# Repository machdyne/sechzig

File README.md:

# Sechzig Compute Module

Sechzig is a work-in-progress compute module specification.

Sechzig modules have a 60-pin 2.54mm card edge connector.

This repo contains detailed specifications as well as relevant KiCad symbols and footprints.

## Specifications

### Signals

This section describes the signals from the perspective of the module when paired with [Mozart](https://github.com/machdyne/mozart).

| Signal | Voltage | Dir | Description |
| ------ | ------- | --- | ----------- |
| PWR5V0 | 5.0V | I | System power (2A max) |
| PWR3V3 | 3.3V | I | System power (1A max) |
| PWRIO | 2.5V - 3.3V | O | I/O power (1A max) |
| SYS\_PG | 3.3V | I | System power good |
| SYS\_RST\_N | PWRIO | I | System reset (active low) |
| SYS\_CLK48 | PWRIO | I | System clock (48MHz) |
| USBD\_Dx | 3.3V | IO | USB device interface |
| USBHx\_Dx | 3.3V | IO | USB host interfaces |
| AUD\_DAT | PWRIO | O | Audio data |
| AUD\_BCK | PWRIO | O | Audio clock |
| AUD\_WS | PWRIO | O | Audio word select |
| ETH\_TXx | PWRIO | O | Ethernet RMII PHY transmit data |
| ETH\_RXx | PWRIO | I | Ethernet RMII PHY receive data |
| ETH\_TXEN | PWRIO | O | Ethernet RMII PHY transmit enable |
| ETH\_CRS\_DV | PWRIO | I | Ethernet RMII PHY carrier sense / receive data valid |
| ETH\_RST\_N | PWRIO | O | Ethernet RMII PHY reset (active low) |
| ETH\_CLK50 | PWRIO | I | Ethernet/video clock (50MHz) |
| DDMI\_xx\_x | 3.3V | O | [DDMI](https://github.com/machdyne/ddmi) interface |
| Xx | PWRIO | IO | Extra link (see notes below) |
| SD\_CD\_N | 3.3V | I | SD card detect (active low) |
| SD\_SS | 3.3V | IO | SD slave select / DAT3 |
| SD\_SCK | 3.3V | O | SD clock |
| SD\_MISO | 3.3V | IO | SD data output / DAT0 |
| SD\_MOSI | 3.3V | IO | SD data input / CMD |
| SD\_D1 | 3.3V| IO | SD DAT1 |
| SD\_D2 | 3.3V | IO | SD DAT2 |
| JTAG\_xxx | PWRIO | IO | JTAG interface |
| UART\_TX | PWRIO | O | UART transmit |
| UART\_RX | PWRIO | I | UART receive |
| DSx\_x | 2.5V | IO | Experimental high-speed link (see notes below) |

#### Signal Notes

  * While all Sechzig modules should be compatible with [Mozart](https://github.com/machdyne/mozart), it is possible to develop alternative host boards that use some signals for other purposes (see [Vivaldi](https://github.com/machdyne/vivaldi) and [Chopin](https://github.com/machdyne/chopin)).

##### Extra Link (Xx) Notes

The purpose of the Xx signals is determined by the host board. For example, on Mozart:

| Signal | Description |
| ------ | ----------- |
| XA | SPI MISO / I2C SCL |
| XB | SPI SCK / I2C SDA |
| XC | SPI MOSI |
| XD | SPI SS |

##### Experimental High-Speed Link (DSx) Notes

The DSx signal traces are routed as length-matched 100 ohm differential pairs. The following minimum required configuration should be supported by all modules, but some modules may have additional capabilities:

| Signal | Standard | Dir | Required | Description |
| ------ | -------- | --- | -------- | ----------- |
| DS0\_x | LVDS25 | IO | N | Transmit and/or Receive |
| DS1\_x | LVDS25 | O | Y | Transmit |
| DS2\_x | LVDS25 | I | Y | Receive |

### Power

Sechzig modules can operate with 2.5V or 3.3V I/O (note that some signals must be 2.5V and 3.3V on all modules). Modules that use 3.3V I/O can simply connect PWRIO to PWR3V3. Modules that use 2.5V I/O must provide 2.5V on PWRIO.

### Module Dimensions

| Dimension | Value |
| --------- | ----- |
| Width | 79mm |
| Height | 50mm max |
| Depth | 8mm max (4mm from center) |
| Card Edge Depth | 1.4mm - 1.6mm |

### Board Revisions

The version number can be found on the back of the module.

#### ML1

Product page for [Sechzig ML1](https://machdyne.com/product/sechzig-ml1-compute-module/).

| Revision | Stackup | Notes |
| -------- | ------- | ----- |
| ML1.1 | Aisler 4L | Initial production version; **Xx signals are not connected** |
| ML1.2 | Aisler 4L | Current production version; connects Xx signals; adds LED |

#### ML2

Product page for [Sechzig ML2](https://machdyne.com/product/sechzig-ml2-compute-module/).

| Revision | Stackup | Notes |
| -------- | ------- | ----- |
| ML2.0 | Aisler 6L | Initial production version |
| ML2.0B | JLC06161H-3313 | Current production version |

#### MX1

Product page for [Sechzig MX1](https://machdyne.com/product/sechzig-mx1-compute-module/).

| Revision | Stackup | Notes |
| -------- | ------- | ----- |
| MX1.1 | Aisler 4L | Initial production version |

#### MX2

Product page for [Sechzig MX2](https://machdyne.com/product/sechzig-mx2-compute-module/).

| Revision | Stackup | Notes |
| -------- | ------- | ----- |
| MX2.0 | JLC06161H-3313 | Initial production version |

## Funding

This project was partially funded through the NGI0 Entrust Fund, a fund established by NLnet with financial support from the European Commission's Next Generation Internet programme.

## License

This project is released under the [CERN-OHL-P](LICENSE.txt) license.

Note: You can use these designs for commercial purposes but we ask that instead of producing exact clones, that you either replace our trademarks and logos with your own or add your own next to ours.

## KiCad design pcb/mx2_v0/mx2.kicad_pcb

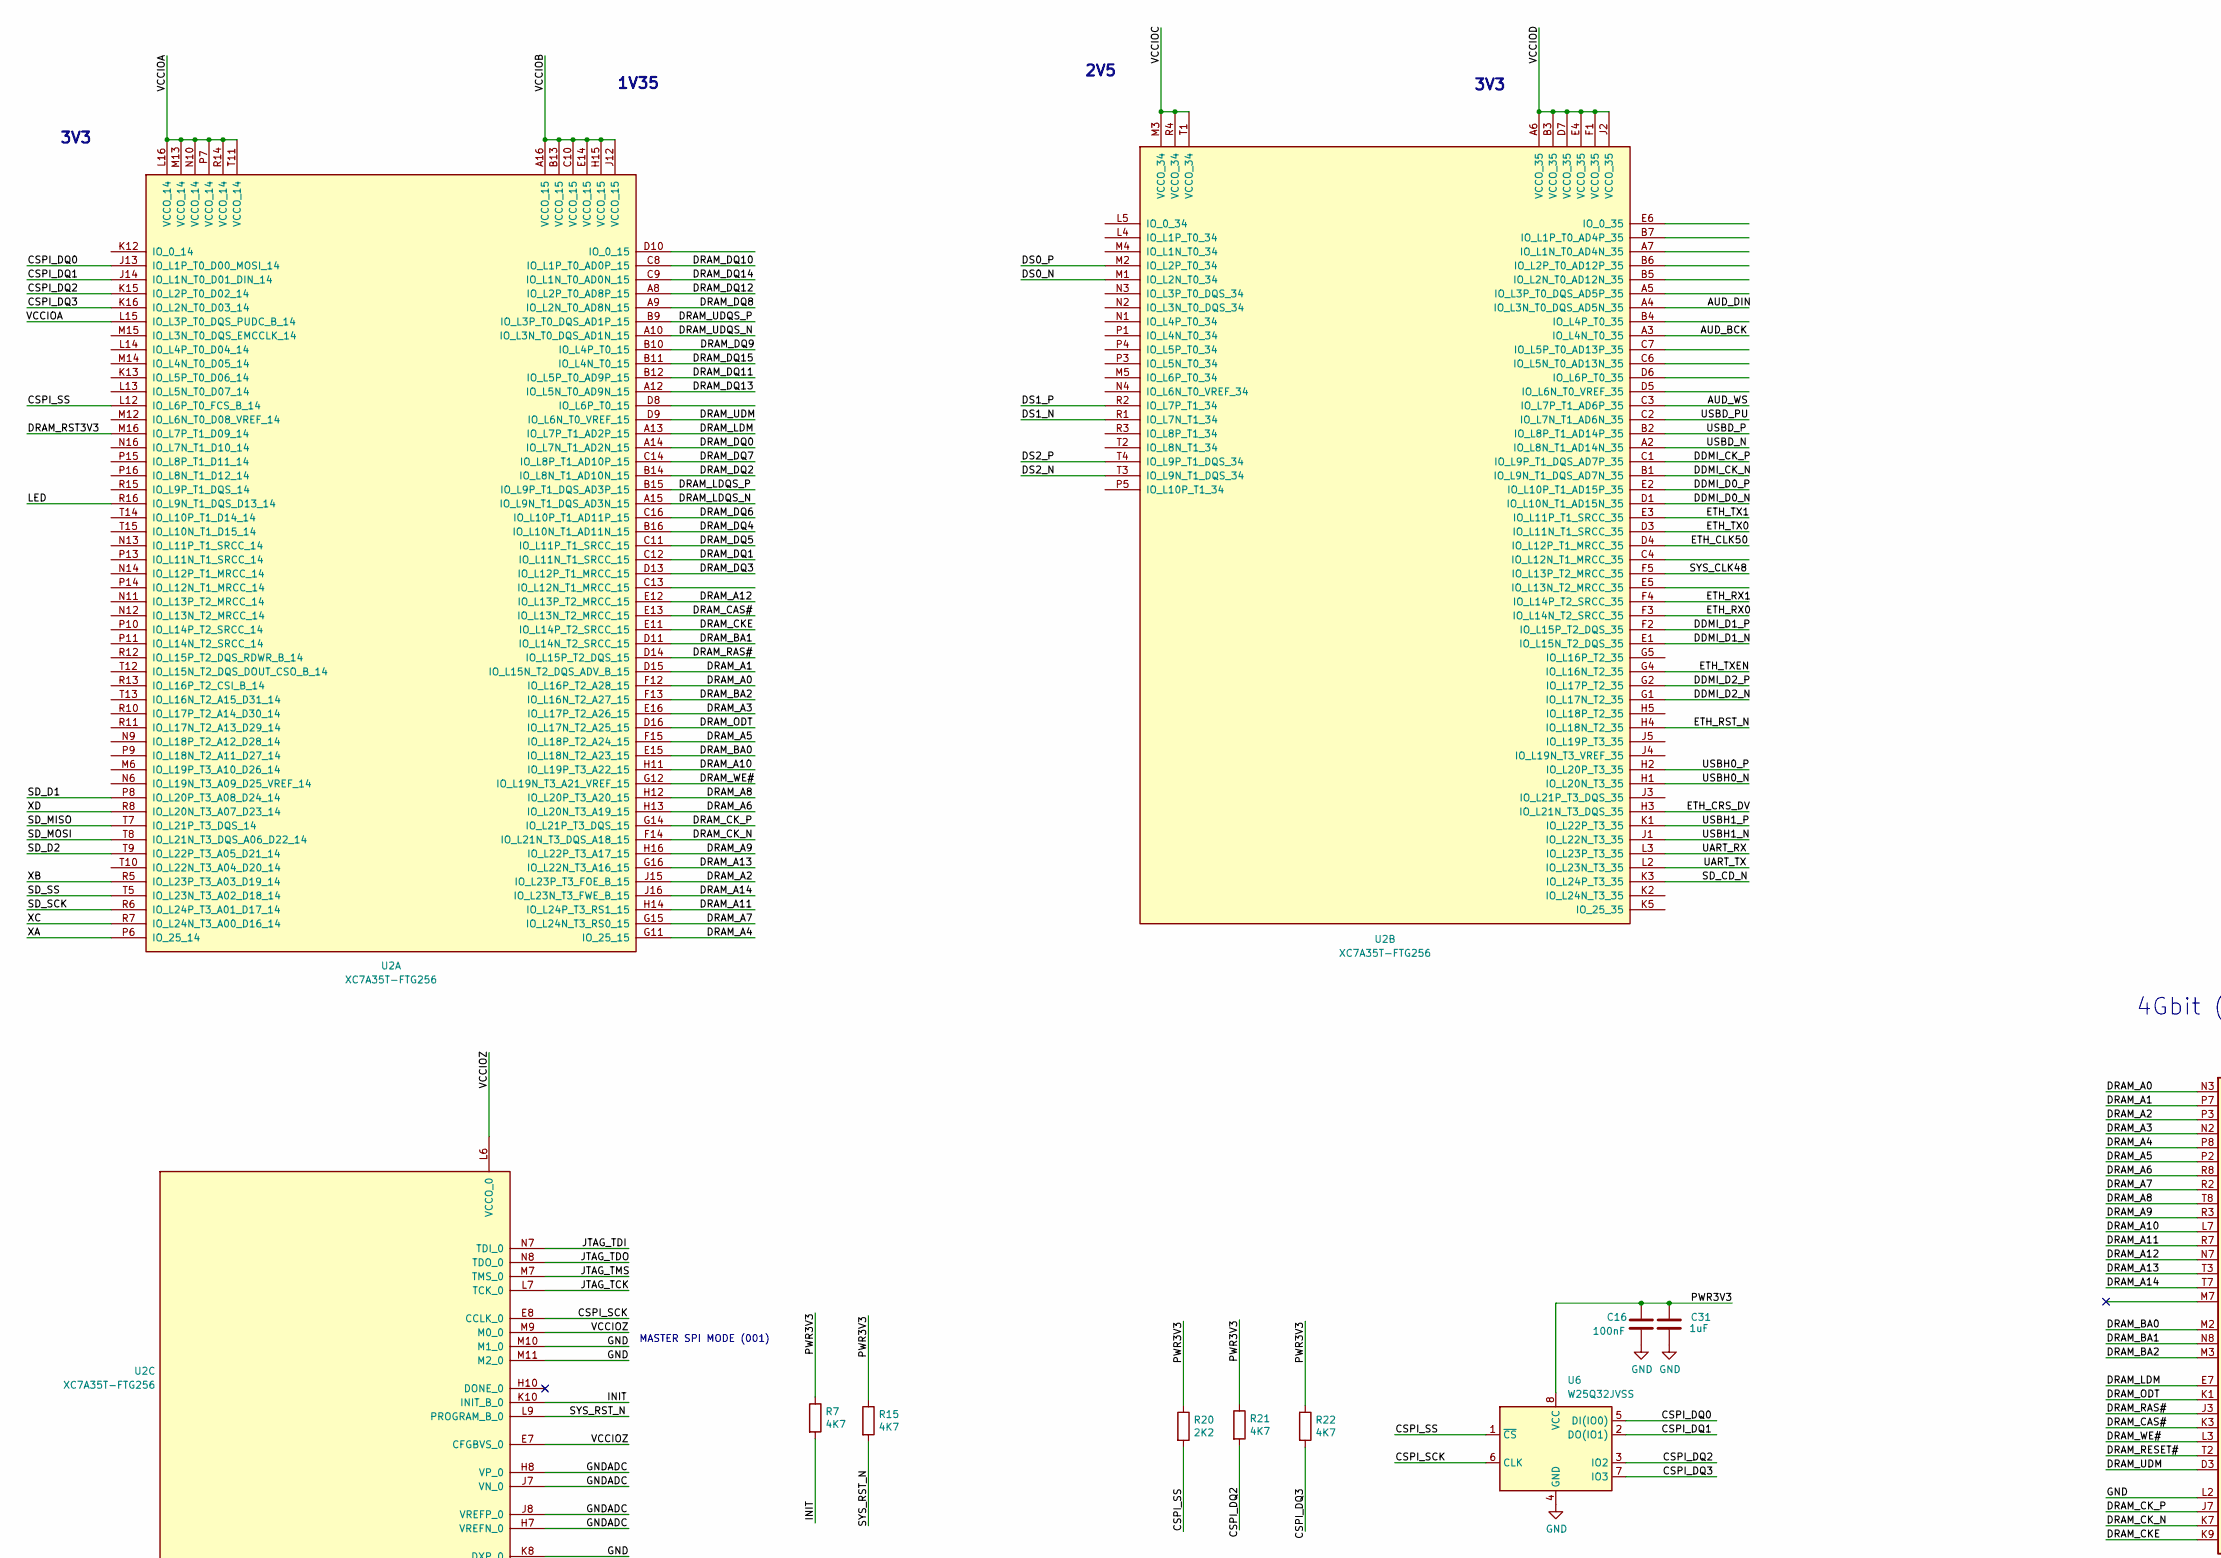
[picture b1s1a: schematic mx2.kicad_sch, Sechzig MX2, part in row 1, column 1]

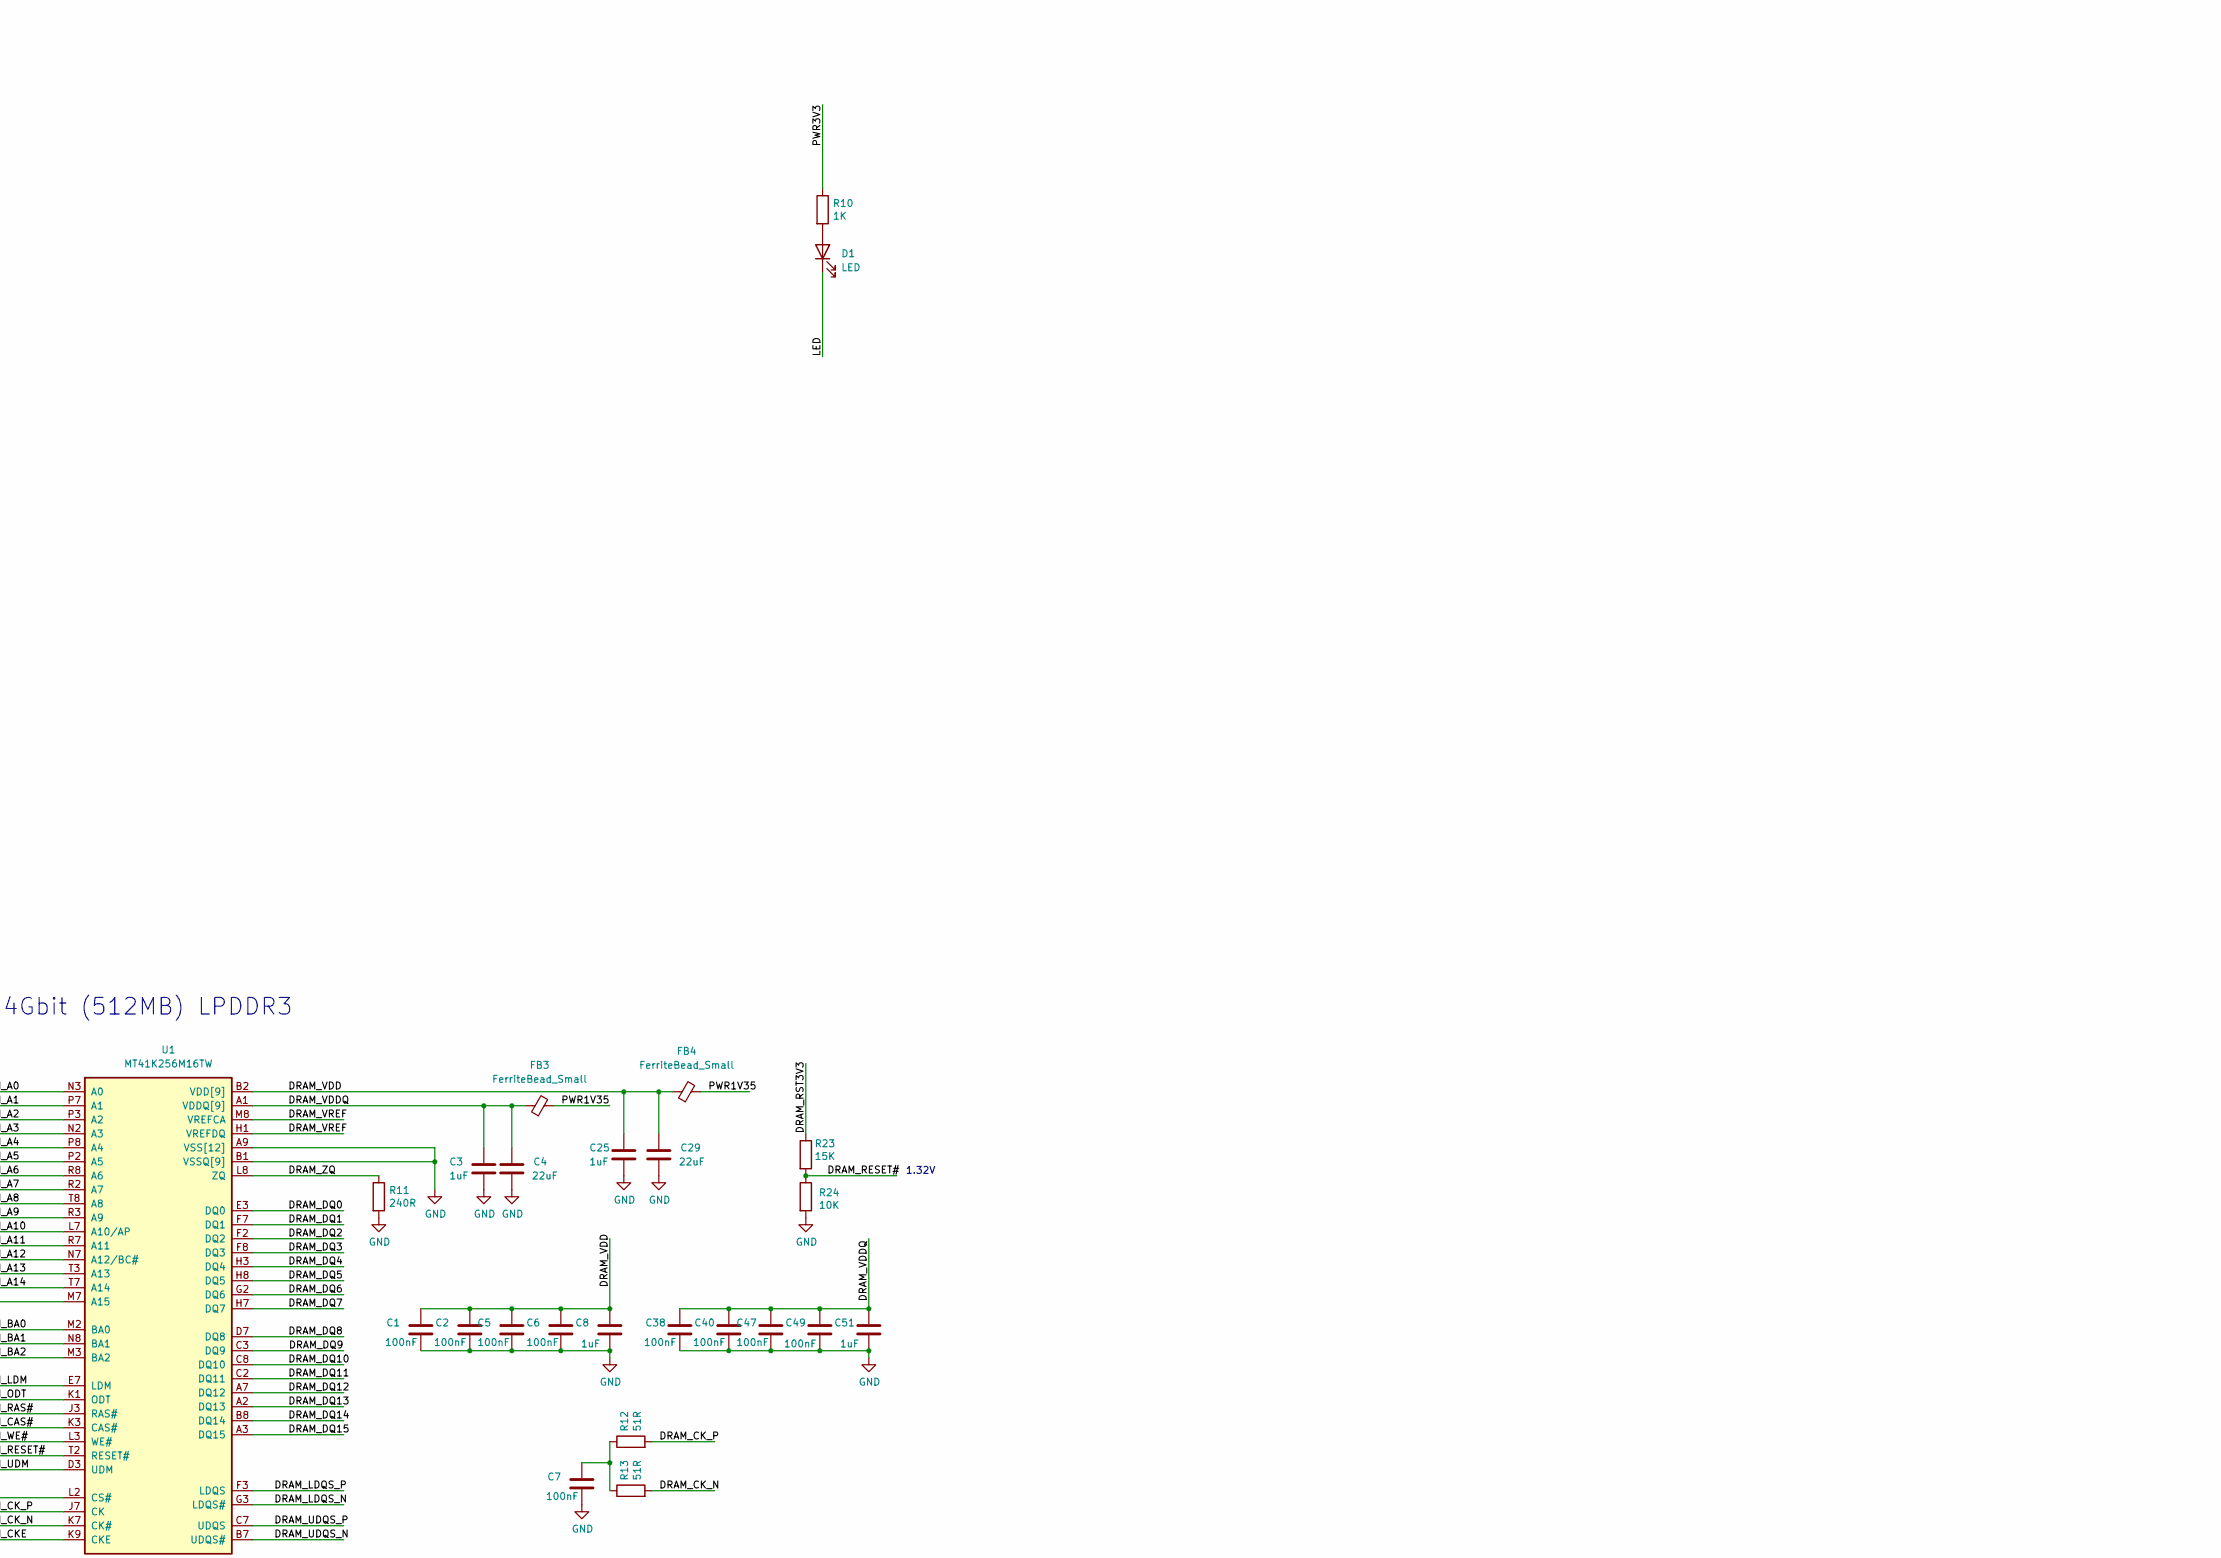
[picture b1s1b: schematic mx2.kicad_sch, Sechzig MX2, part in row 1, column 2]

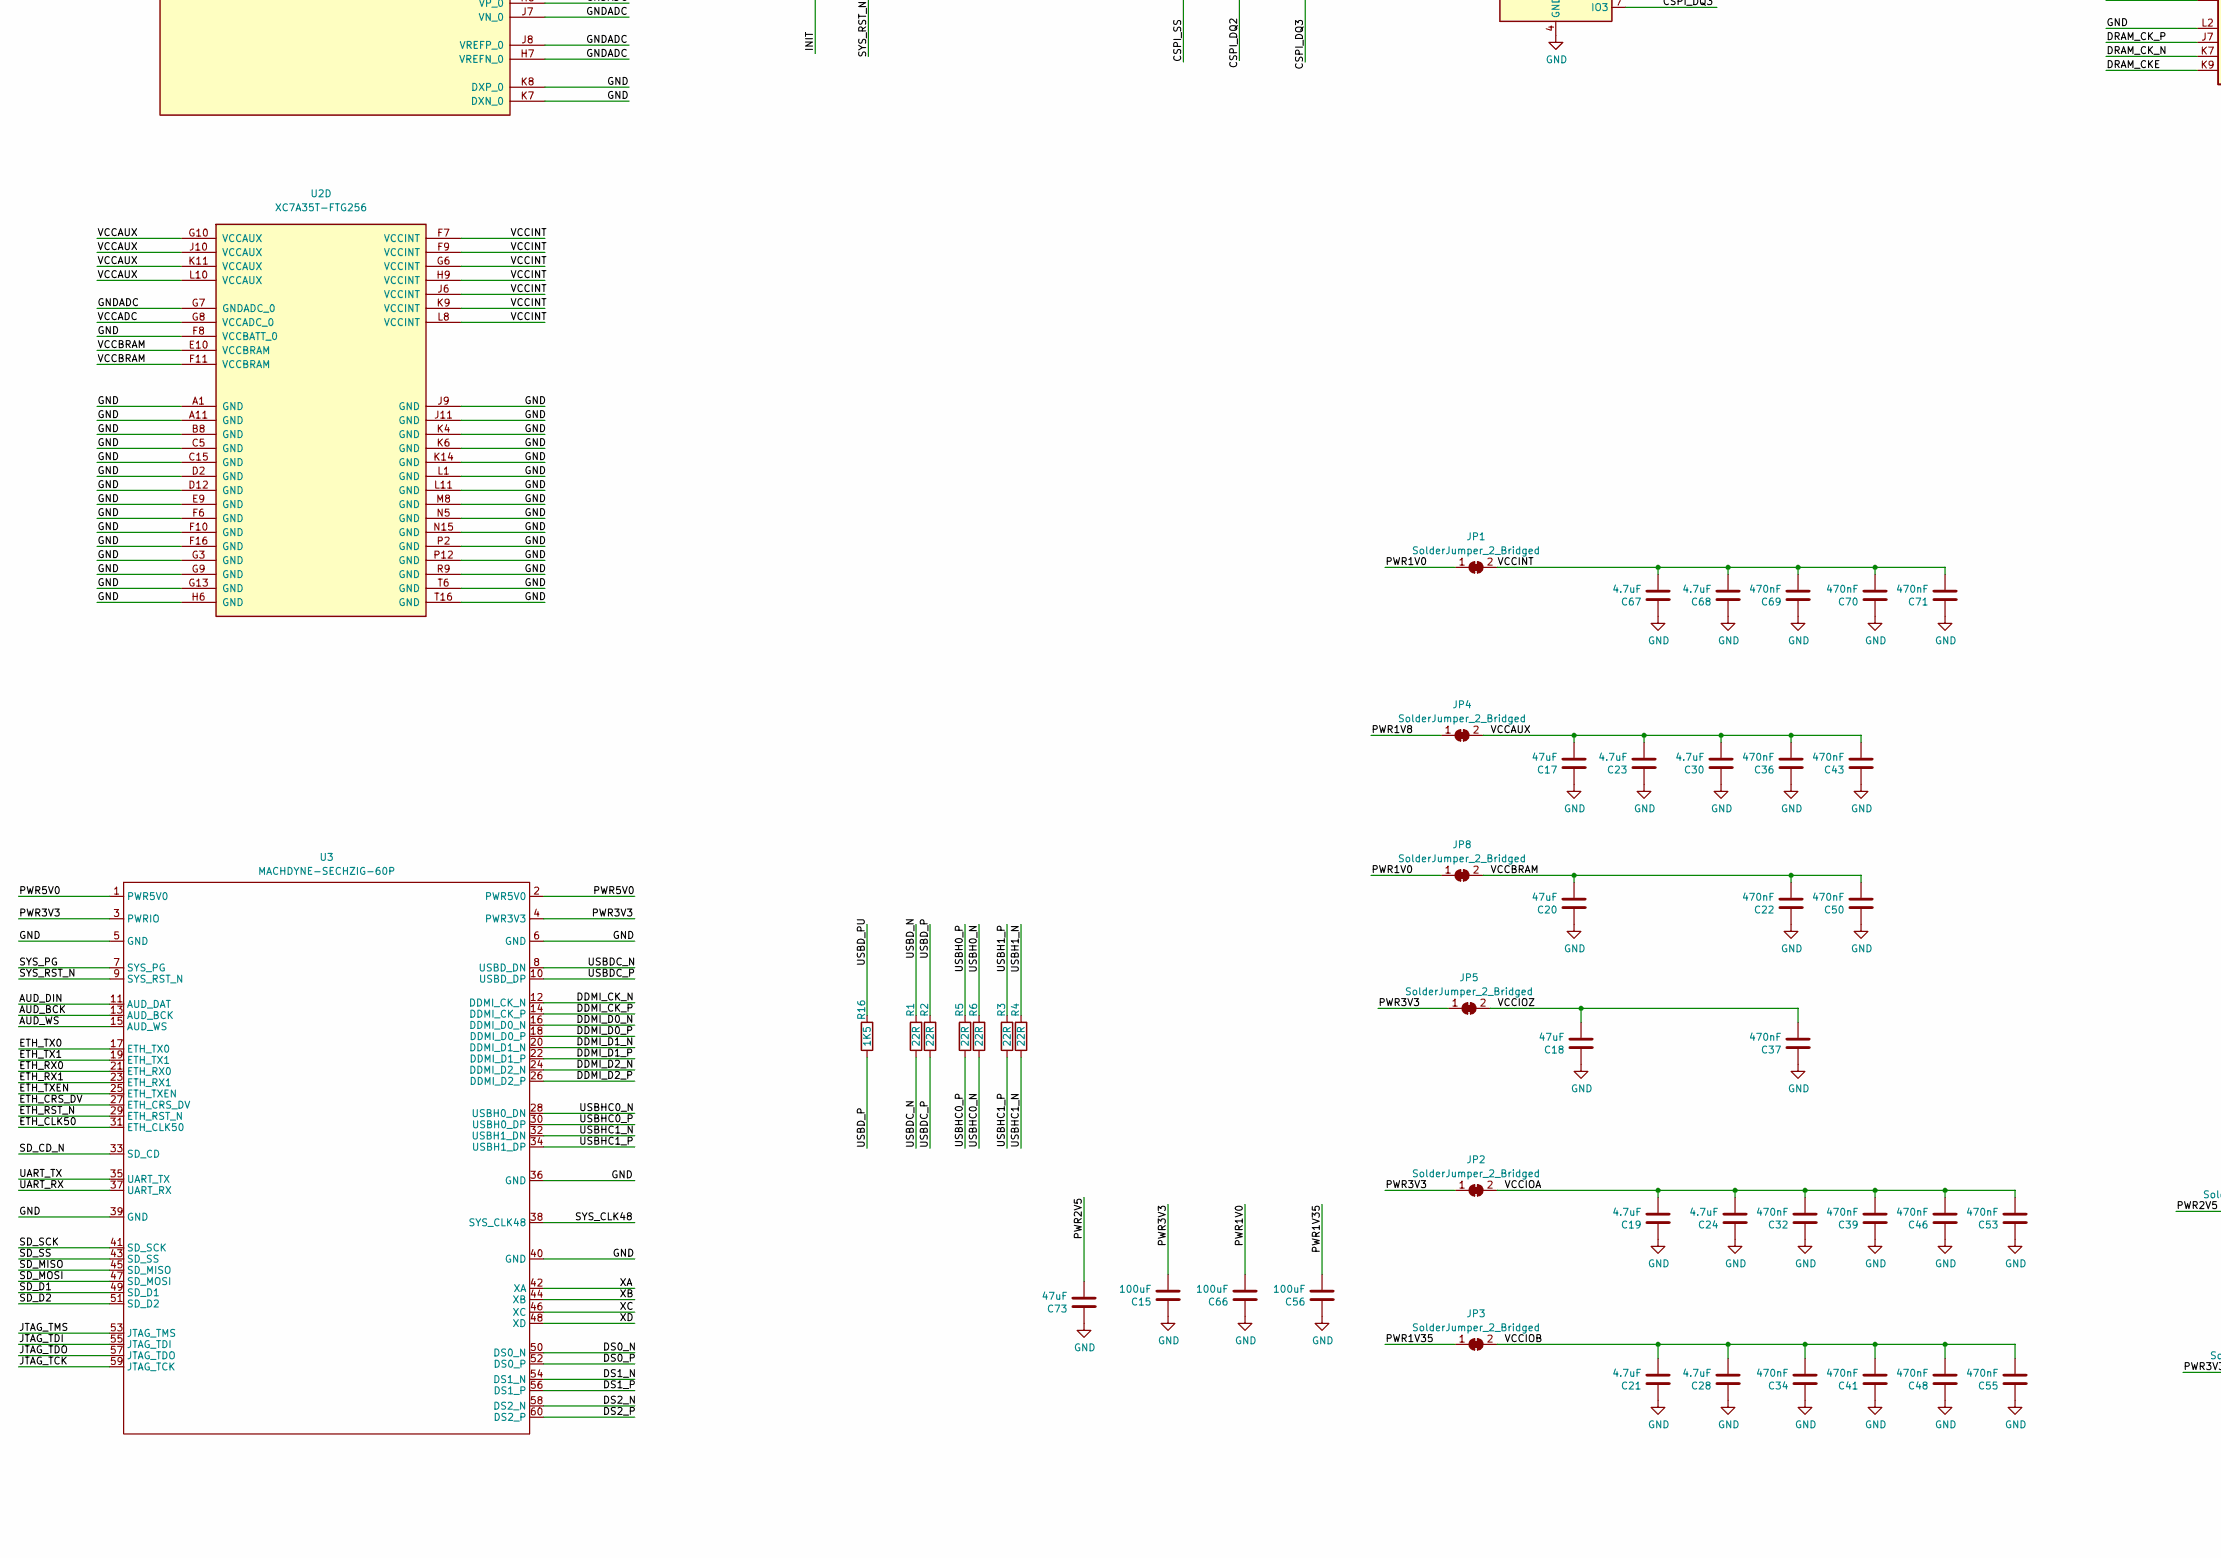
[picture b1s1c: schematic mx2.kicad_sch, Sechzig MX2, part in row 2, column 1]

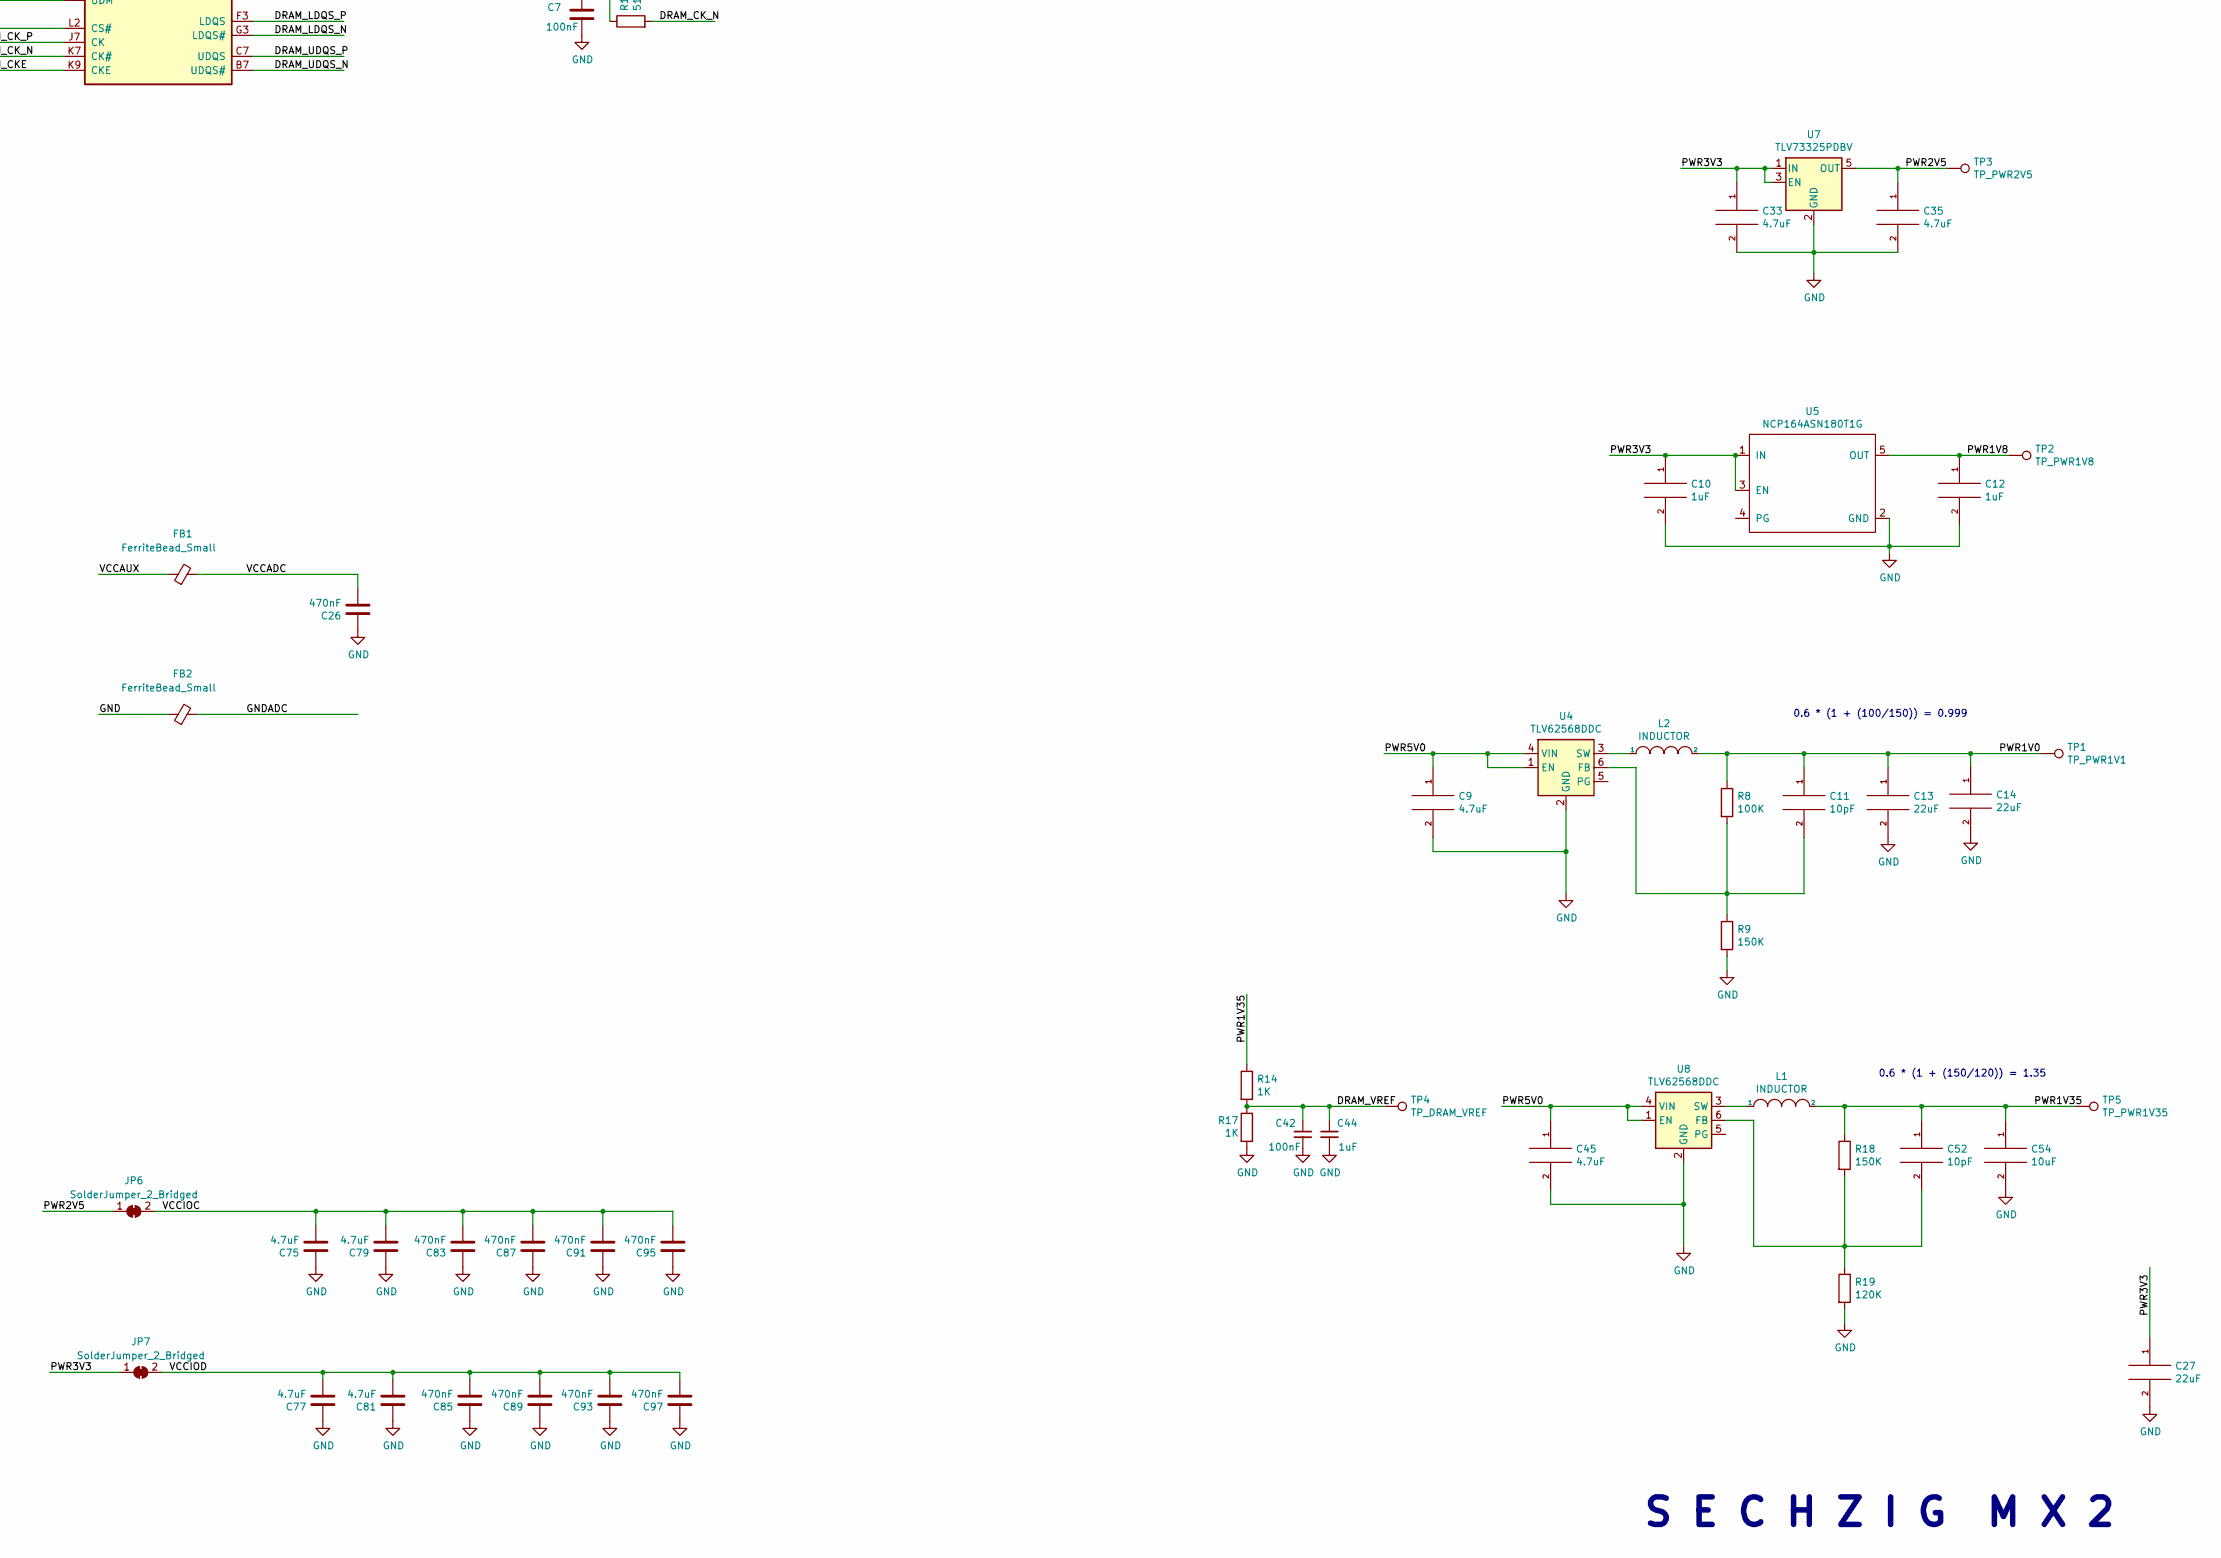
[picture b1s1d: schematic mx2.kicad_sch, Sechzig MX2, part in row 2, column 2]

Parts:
C1, C2, C5, C6, C7, C38, C40, C47, C49: 100nF; C_0402_1005Metric
C3, C8, C25, C51: 1uF; C_0402_1005Metric
C4, C13, C14, C27, C29: 22uF; C_0603_1608Metric
C9, C19, C21, C23, C24, C28, C30, C33, C35, C45, C67, C68, C75, C77, C79, C81: 4.7uF; C_0603_1608Metric
C10, C12, C31, C44: 1uF; C_0603_1608Metric
C11, C52: 10pF; C_0603_1608Metric
C15, C56, C66: 100uF; C_1206_3216Metric
C16, C42: 100nF; C_0603_1608Metric
C17, C18, C20, C73: 47uF; C_0603_1608Metric
C22, C32, C34, C39, C41, C46, C83, C85, C87, C93: 470nF; C_0603_1608Metric
C26, C36, C37, C48, C53, C69, C70, C89, C91, C95, C97: 470nF; C_0402_1005Metric
C43, C50, C55, C71: 470nF; C_0201_0603Metric
C54: 10uF; C_0603_1608Metric
D1: LED; LED_0603_1608Metric
FB1, FB2: FerriteBead_Small; L_0402_1005Metric
FB3, FB4: FerriteBead_Small; R_0603_1608Metric
JP1, JP2, JP3, JP4, JP5, JP6, JP7, JP8: SolderJumper_2_Bridged; LD-NETTIE-0603
L1, L2: INDUCTOR; L_0805_2012Metric
R1, R2, R3, R4, R5, R6: 22R; R_0402_1005Metric
R7, R15, R21, R22: 4K7; R_0603_1608Metric
R8: 100K; R_0603_1608Metric
R9, R18: 150K; R_0603_1608Metric
R10, R14, R17: 1K; R_0603_1608Metric
R11: 240R; R_0603_1608Metric
R12, R13: 51R; R_0402_1005Metric
R16: 1K5; R_0402_1005Metric
R19: 120K; R_0603_1608Metric
R20: 2K2; R_0603_1608Metric
R23: 15K; R_0402_1005Metric
R24: 10K; R_0402_1005Metric
TP1: TP_PWR1V1; TestPoint_THTPad_D1.0mm_Drill0.5mm
TP2: TP_PWR1V8; TestPoint_THTPad_D1.0mm_Drill0.5mm
TP3: TP_PWR2V5; TestPoint_THTPad_D1.0mm_Drill0.5mm
TP4: TP_DRAM_VREF; TestPoint_THTPad_D1.0mm_Drill0.5mm
TP5: TP_PWR1V35; TestPoint_THTPad_D1.0mm_Drill0.5mm
U1: MT41K256M16TW; BGA-96_9.0x13.0mm_Layout2x3x16_P0.8mm_FIXED_SILK
U2: XC7A35T-FTG256; BGA-256_17.0x17.0mm_Layout16x16_P1.0mm_Ball0.5mm_Pad0.5mm_N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
U3: MACHDYNE-SECHZIG-60P; MACHDYNE_EDGE_60P
U4, U8: TLV62568DDC; SOT-23-6
U5: NCP164ASN180T1G; SOT-23-5
U6: W25Q32JVSS; SOIC-8_3.9x4.9mm_P1.27mm
U7: TLV73325PDBV; SOT-23-5

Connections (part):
/AUD_BCK: U2.A3 (IO_L4N_T0_35), U3.13 (AUD_BCK)
/AUD_DIN: U2.A4 (IO_L3N_T0_DQS_AD5N_35), U3.11 (AUD_DAT)
/AUD_WS: U2.C3 (IO_L7P_T1_AD6P_35), U3.15 (AUD_WS)
/CSPI_DQ0: U2.J13 (IO_L1P_T0_D00_MOSI_14), U6.5 (DI(IO0))
/CSPI_DQ1: U2.J14 (IO_L1N_T0_D01_DIN_14), U6.2 (DO(IO1))
/CSPI_DQ2: R21.2, U2.K15 (IO_L2P_T0_D02_14), U6.3 (IO2)
/CSPI_DQ3: R22.2, U2.K16 (IO_L2N_T0_D03_14), U6.7 (IO3)
/CSPI_SCK: U2.E8 (CCLK_0), U6.6 (CLK)
/CSPI_SS: R20.2, U2.L12 (IO_L6P_T0_FCS_B_14), U6.1 (~CS)
/DDMI_CK_N: U2.B1 (IO_L9N_T1_DQS_AD7N_35), U3.12 (DDMI_CK_N)
/DDMI_CK_P: U2.C1 (IO_L9P_T1_DQS_AD7P_35), U3.14 (DDMI_CK_P)
/DDMI_D0_N: U2.D1 (IO_L10N_T1_AD15N_35), U3.16 (DDMI_D0_N)
/DDMI_D0_P: U2.E2 (IO_L10P_T1_AD15P_35), U3.18 (DDMI_D0_P)
/DDMI_D1_N: U2.E1 (IO_L15N_T2_DQS_35), U3.20 (DDMI_D1_N)
/DDMI_D1_P: U2.F2 (IO_L15P_T2_DQS_35), U3.22 (DDMI_D1_P)
/DDMI_D2_N: U2.G1 (IO_L17N_T2_35), U3.24 (DDMI_D2_N)
/DDMI_D2_P: U2.G2 (IO_L17P_T2_35), U3.26 (DDMI_D2_P)
/DRAM_A0: U1.N3 (A0), U2.F12 (IO_L16P_T2_A28_15)
/DRAM_A1: U1.P7 (A1), U2.D15 (IO_L15N_T2_DQS_ADV_B_15)
/DRAM_A2: U1.P3 (A2), U2.J15 (IO_L23P_T3_FOE_B_15)
/DRAM_A3: U1.N2 (A3), U2.E16 (IO_L17P_T2_A26_15)
/DRAM_A4: U1.P8 (A4), U2.G11 (IO_25_15)
/DRAM_A5: U1.P2 (A5), U2.F15 (IO_L18P_T2_A24_15)
/DRAM_A6: U1.R8 (A6), U2.H13 (IO_L20N_T3_A19_15)
/DRAM_A7: U1.R2 (A7), U2.G15 (IO_L24N_T3_RS0_15)
/DRAM_A8: U1.T8 (A8), U2.H12 (IO_L20P_T3_A20_15)
/DRAM_A9: U1.R3 (A9), U2.H16 (IO_L22P_T3_A17_15)
/DRAM_A10: U1.L7 (A10/AP), U2.H11 (IO_L19P_T3_A22_15)
/DRAM_A11: U1.R7 (A11), U2.H14 (IO_L24P_T3_RS1_15)
/DRAM_A12: U1.N7 (A12/BC#), U2.E12 (IO_L13P_T2_MRCC_15)
/DRAM_A13: U1.T3 (A13), U2.G16 (IO_L22N_T3_A16_15)
/DRAM_A14: U1.T7 (A14), U2.J16 (IO_L23N_T3_FWE_B_15)
/DRAM_BA0: U1.M2 (BA0), U2.E15 (IO_L18N_T2_A23_15)
/DRAM_BA1: U1.N8 (BA1), U2.D11 (IO_L14N_T2_SRCC_15)
/DRAM_BA2: U1.M3 (BA2), U2.F13 (IO_L16N_T2_A27_15)
/DRAM_CAS#: U1.K3 (CAS#), U2.E13 (IO_L13N_T2_MRCC_15)
/DRAM_CKE: U1.K9 (CKE), U2.E11 (IO_L14P_T2_SRCC_15)
/DRAM_CK_N: R13.2, U1.K7 (CK#), U2.F14 (IO_L21N_T3_DQS_A18_15)
/DRAM_CK_P: R12.2, U1.J7 (CK), U2.G14 (IO_L21P_T3_DQS_15)
/DRAM_DQ0: U1.E3 (DQ0), U2.A14 (IO_L7N_T1_AD2N_15)
/DRAM_DQ1: U1.F7 (DQ1), U2.C12 (IO_L11N_T1_SRCC_15)
/DRAM_DQ2: U1.F2 (DQ2), U2.B14 (IO_L8N_T1_AD10N_15)
/DRAM_DQ3: U1.F8 (DQ3), U2.D13 (IO_L12P_T1_MRCC_15)
/DRAM_DQ4: U1.H3 (DQ4), U2.B16 (IO_L10N_T1_AD11N_15)
/DRAM_DQ5: U1.H8 (DQ5), U2.C11 (IO_L11P_T1_SRCC_15)
/DRAM_DQ6: U1.G2 (DQ6), U2.C16 (IO_L10P_T1_AD11P_15)
/DRAM_DQ7: U1.H7 (DQ7), U2.C14 (IO_L8P_T1_AD10P_15)
/DRAM_DQ8: U1.D7 (DQ8), U2.A9 (IO_L2N_T0_AD8N_15)
/DRAM_DQ9: U1.C3 (DQ9), U2.B10 (IO_L4P_T0_15)
/DRAM_DQ10: U1.C8 (DQ10), U2.C8 (IO_L1P_T0_AD0P_15)
/DRAM_DQ11: U1.C2 (DQ11), U2.B12 (IO_L5P_T0_AD9P_15)
/DRAM_DQ12: U1.A7 (DQ12), U2.A8 (IO_L2P_T0_AD8P_15)
/DRAM_DQ13: U1.A2 (DQ13), U2.A12 (IO_L5N_T0_AD9N_15)
/DRAM_DQ14: U1.B8 (DQ14), U2.C9 (IO_L1N_T0_AD0N_15)
/DRAM_DQ15: U1.A3 (DQ15), U2.B11 (IO_L4N_T0_15)
/DRAM_LDM: U1.E7 (LDM), U2.A13 (IO_L7P_T1_AD2P_15)
/DRAM_LDQS_N: U1.G3 (LDQS#), U2.A15 (IO_L9N_T1_DQS_AD3N_15)
/DRAM_LDQS_P: U1.F3 (LDQS), U2.B15 (IO_L9P_T1_DQS_AD3P_15)
/DRAM_ODT: U1.K1 (ODT), U2.D16 (IO_L17N_T2_A25_15)
/DRAM_RAS#: U1.J3 (RAS#), U2.D14 (IO_L15P_T2_DQS_15)
/DRAM_RESET#: R23.2, R24.1, U1.T2 (RESET#)
/DRAM_RST3V3: R23.1, U2.M16 (IO_L7P_T1_D09_14)
/DRAM_UDM: U1.D3 (UDM), U2.D9 (IO_L6N_T0_VREF_15)
/DRAM_UDQS_N: U1.B7 (UDQS#), U2.A10 (IO_L3N_T0_DQS_AD1N_15)
/DRAM_UDQS_P: U1.C7 (UDQS), U2.B9 (IO_L3P_T0_DQS_AD1P_15)
/DRAM_VDD: C1.1, C2.1, C5.1, C6.1, C8.1, C25.1, C29.1, FB4.1, U1.B2 (VDD[9]), U1.D9 (VDD), U1.G7 (VDD), U1.K2 (VDD), U1.K8 (VDD), U1.N1 (VDD), U1.N9 (VDD), U1.R1 (VDD), U1.R9 (VDD)
/DRAM_VDDQ: C3.1, C4.1, C38.1, C40.1, C47.1, C49.1, C51.1, FB3.1, U1.A1 (VDDQ[9]), U1.A8 (VDDQ), U1.C1 (VDDQ), U1.C9 (VDDQ), U1.D2 (VDDQ), U1.E9 (VDDQ), U1.F1 (VDDQ), U1.H2 (VDDQ), U1.H9 (VDDQ)
/DRAM_VREF: C42.1, C44.1, R14.2, R17.1, TP4.1, U1.H1 (VREFDQ), U1.M8 (VREFCA)
/DRAM_WE#: U1.L3 (WE#), U2.G12 (IO_L19N_T3_A21_VREF_15)
/DRAM_ZQ: R11.1, U1.L8 (ZQ)
/DS0_N: U2.M1 (IO_L2N_T0_34), U3.50 (DS0_N)
/DS0_P: U2.M2 (IO_L2P_T0_34), U3.52 (DS0_P)
/DS1_N: U2.R1 (IO_L7N_T1_34), U3.54 (DS1_N)
/DS1_P: U2.R2 (IO_L7P_T1_34), U3.56 (DS1_P)
/DS2_N: U2.T3 (IO_L9N_T1_DQS_34), U3.58 (DS2_N)
/DS2_P: U2.T4 (IO_L9P_T1_DQS_34), U3.60 (DS2_P)
/ETH_CLK50: U2.D4 (IO_L12P_T1_MRCC_35), U3.31 (ETH_CLK50)
/ETH_CRS_DV: U2.H3 (IO_L21N_T3_DQS_35), U3.27 (ETH_CRS_DV)
/ETH_RST_N: U2.H4 (IO_L18N_T2_35), U3.29 (ETH_RST_N)
/ETH_RX0: U2.F3 (IO_L14N_T2_SRCC_35), U3.21 (ETH_RX0)
/ETH_RX1: U2.F4 (IO_L14P_T2_SRCC_35), U3.23 (ETH_RX1)
/ETH_TX0: U2.D3 (IO_L11N_T1_SRCC_35), U3.17 (ETH_TX0)
/ETH_TX1: U2.E3 (IO_L11P_T1_SRCC_35), U3.19 (ETH_TX1)
/ETH_TXEN: U2.G4 (IO_L16N_T2_35), U3.25 (ETH_TXEN)
/GNDADC: FB2.2, U2.G7 (GNDADC_0), U2.H7 (VREFN_0), U2.H8 (VP_0), U2.J7 (VN_0), U2.J8 (VREFP_0)
/INIT: R7.2, U2.K10 (INIT_B_0)
/JTAG_TCK: U2.L7 (TCK_0), U3.59 (JTAG_TCK)
/JTAG_TDI: U2.N7 (TDI_0), U3.55 (JTAG_TDI)
/JTAG_TDO: U2.N8 (TDO_0), U3.57 (JTAG_TDO)
/JTAG_TMS: U2.M7 (TMS_0), U3.53 (JTAG_TMS)
/LED: D1.1 (K), U2.R16 (IO_L9N_T1_DQS_D13_14)
/PWR1V0: C11.1, C13.1, C14.1, C66.2, JP1.1 (A), JP8.1 (A), L2.2, R8.1, TP1.1
/PWR1V8: C12.1, JP4.1 (A), TP2.1, U5.5 (OUT)
/PWR1V35: C52.1, C54.1, C56.2, FB3.2, FB4.2, JP3.1 (A), L1.2, R14.1, R18.1, TP5.1
/PWR2V5: C35.1, C73.2, JP6.1 (A), TP3.1, U7.5 (OUT)
/PWR3V3: C10.1, C15.2, C16.1, C27.1, C31.1, C33.1, JP2.1 (A), JP5.1 (A), JP7.1 (A), R7.1, R10.1, R15.1, R20.1, R21.1, R22.1, U3.3 (PWRIO), U3.4 (PWR3V3), U5.1 (IN), U5.3 (EN), U6.8 (VCC), U7.1 (IN), U7.3 (EN)
/PWR5V0: C9.1, C45.1, U3.1 (PWR5V0), U3.2 (PWR5V0), U4.1 (EN), U4.4 (VIN), U8.1 (EN), U8.4 (VIN)
/SD_CD_N: U2.K3 (IO_L24P_T3_35), U3.33 (SD_CD)
/SD_D1: U2.P8 (IO_L20P_T3_A08_D24_14), U3.49 (SD_D1)
/SD_D2: U2.T9 (IO_L22P_T3_A05_D21_14), U3.51 (SD_D2)
/SD_MISO: U2.T7 (IO_L21P_T3_DQS_14), U3.45 (SD_MISO)
/SD_MOSI: U2.T8 (IO_L21N_T3_DQS_A06_D22_14), U3.47 (SD_MOSI)
/SD_SCK: U2.R6 (IO_L24P_T3_A01_D17_14), U3.41 (SD_SCK)
/SD_SS: U2.T5 (IO_L23N_T3_A02_D18_14), U3.43 (SD_SS)
/SYS_CLK48: U2.F5 (IO_L13P_T2_MRCC_35), U3.38 (SYS_CLK48)
/SYS_PG: U3.7 (SYS_PG)
/SYS_RST_N: R15.2, U2.L9 (PROGRAM_B_0), U3.9 (SYS_RST_N)
/UART_RX: U2.L3 (IO_L23P_T3_35), U3.37 (UART_RX)
/UART_TX: U2.L2 (IO_L23N_T3_35), U3.35 (UART_TX)
/USBDC_N: R1.1, U3.8 (USBD_DN)
/USBDC_P: R2.1, U3.10 (USBD_DP)
/USBD_N: R1.2, U2.A2 (IO_L8N_T1_AD14N_35)
/USBD_P: R2.2, R16.1, U2.B2 (IO_L8P_T1_AD14P_35)
/USBD_PU: R16.2, U2.C2 (IO_L7N_T1_AD6N_35)
/USBH0_N: R6.2, U2.H1 (IO_L20N_T3_35)
/USBH0_P: R5.2, U2.H2 (IO_L20P_T3_35)
/USBH1_N: R4.2, U2.J1 (IO_L22N_T3_35)
/USBH1_P: R3.2, U2.K1 (IO_L22P_T3_35)
/USBHC0_N: R6.1, U3.28 (USBH0_DN)
/USBHC0_P: R5.1, U3.30 (USBH0_DP)
/USBHC1_N: R4.1, U3.32 (USBH1_DN)
/USBHC1_P: R3.1, U3.34 (USBH1_DP)
/VCCADC: C26.2, FB1.2, U2.G8 (VCCADC_0)
/VCCAUX: C17.2, C23.2, C30.2, C36.2, C43.2, FB1.1, JP4.2 (B), U2.G10 (VCCAUX), U2.J10 (VCCAUX), U2.K11 (VCCAUX), U2.L10 (VCCAUX)
/VCCBRAM: C20.2, C22.2, C50.2, JP8.2 (B), U2.E10 (VCCBRAM), U2.F11 (VCCBRAM)
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
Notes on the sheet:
3V3
S E C H Z I G M X 2
1V35
1.32V
0.6 * (1 + (100/150)) = 0.999
4Gbit (512MB) LPDDR3
0.6 * (1 + (150/120)) = 1.35
MASTER SPI MODE (001)
2V5

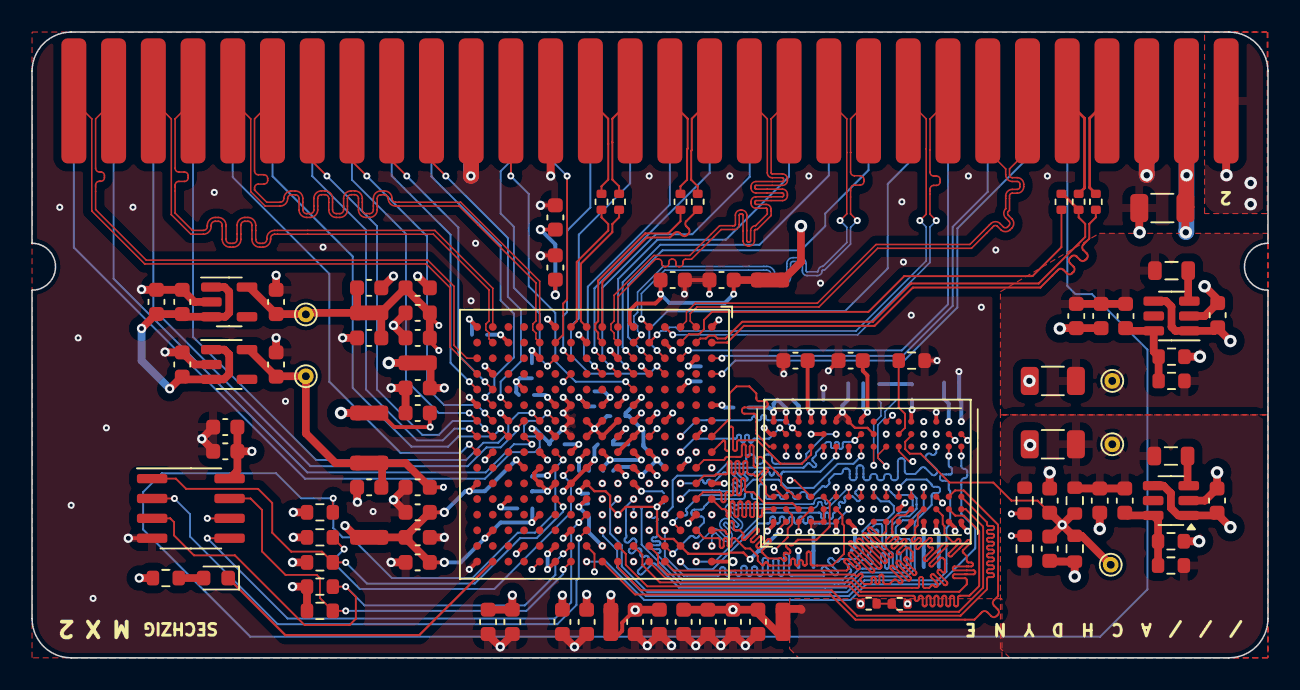
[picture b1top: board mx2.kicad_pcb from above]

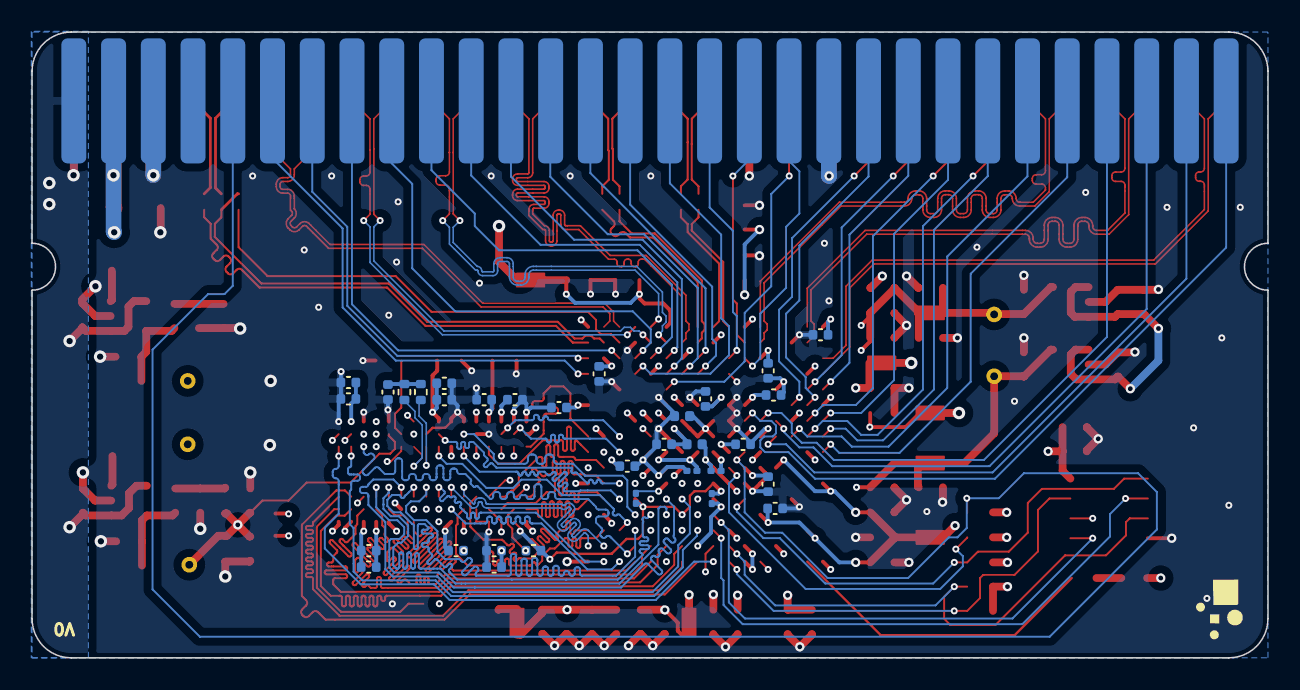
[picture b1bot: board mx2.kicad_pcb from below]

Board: 6 copper layers, 79.0 x 40.0 mm, 127 parts (33 on the bottom side), 141 nets.

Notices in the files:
pcb/ml1/ml1.kicad_sch:
Copyright © 2023 Lone Dynamics Corporation
pcb/mx2_v0/mx2.kicad_sch:
Copyright © 2024 Lone Dynamics Corporation
